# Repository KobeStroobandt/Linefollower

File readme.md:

# LineFollower

lege repository die je als template kan gebruiken om een eigen repository te starten voor uw linefollower project

## specifications

microcontroller: ESP32 S3

motors: Aslong JGA12-N20-30

h-bridge: TB6612FNG

sensors: Polulu QTR 8

batteries: 1800 Top Fuel

wireless communication: Wifi

distance sensor - motors: 7cm

weight: 0.5 kg

speed: 0.56 m/s

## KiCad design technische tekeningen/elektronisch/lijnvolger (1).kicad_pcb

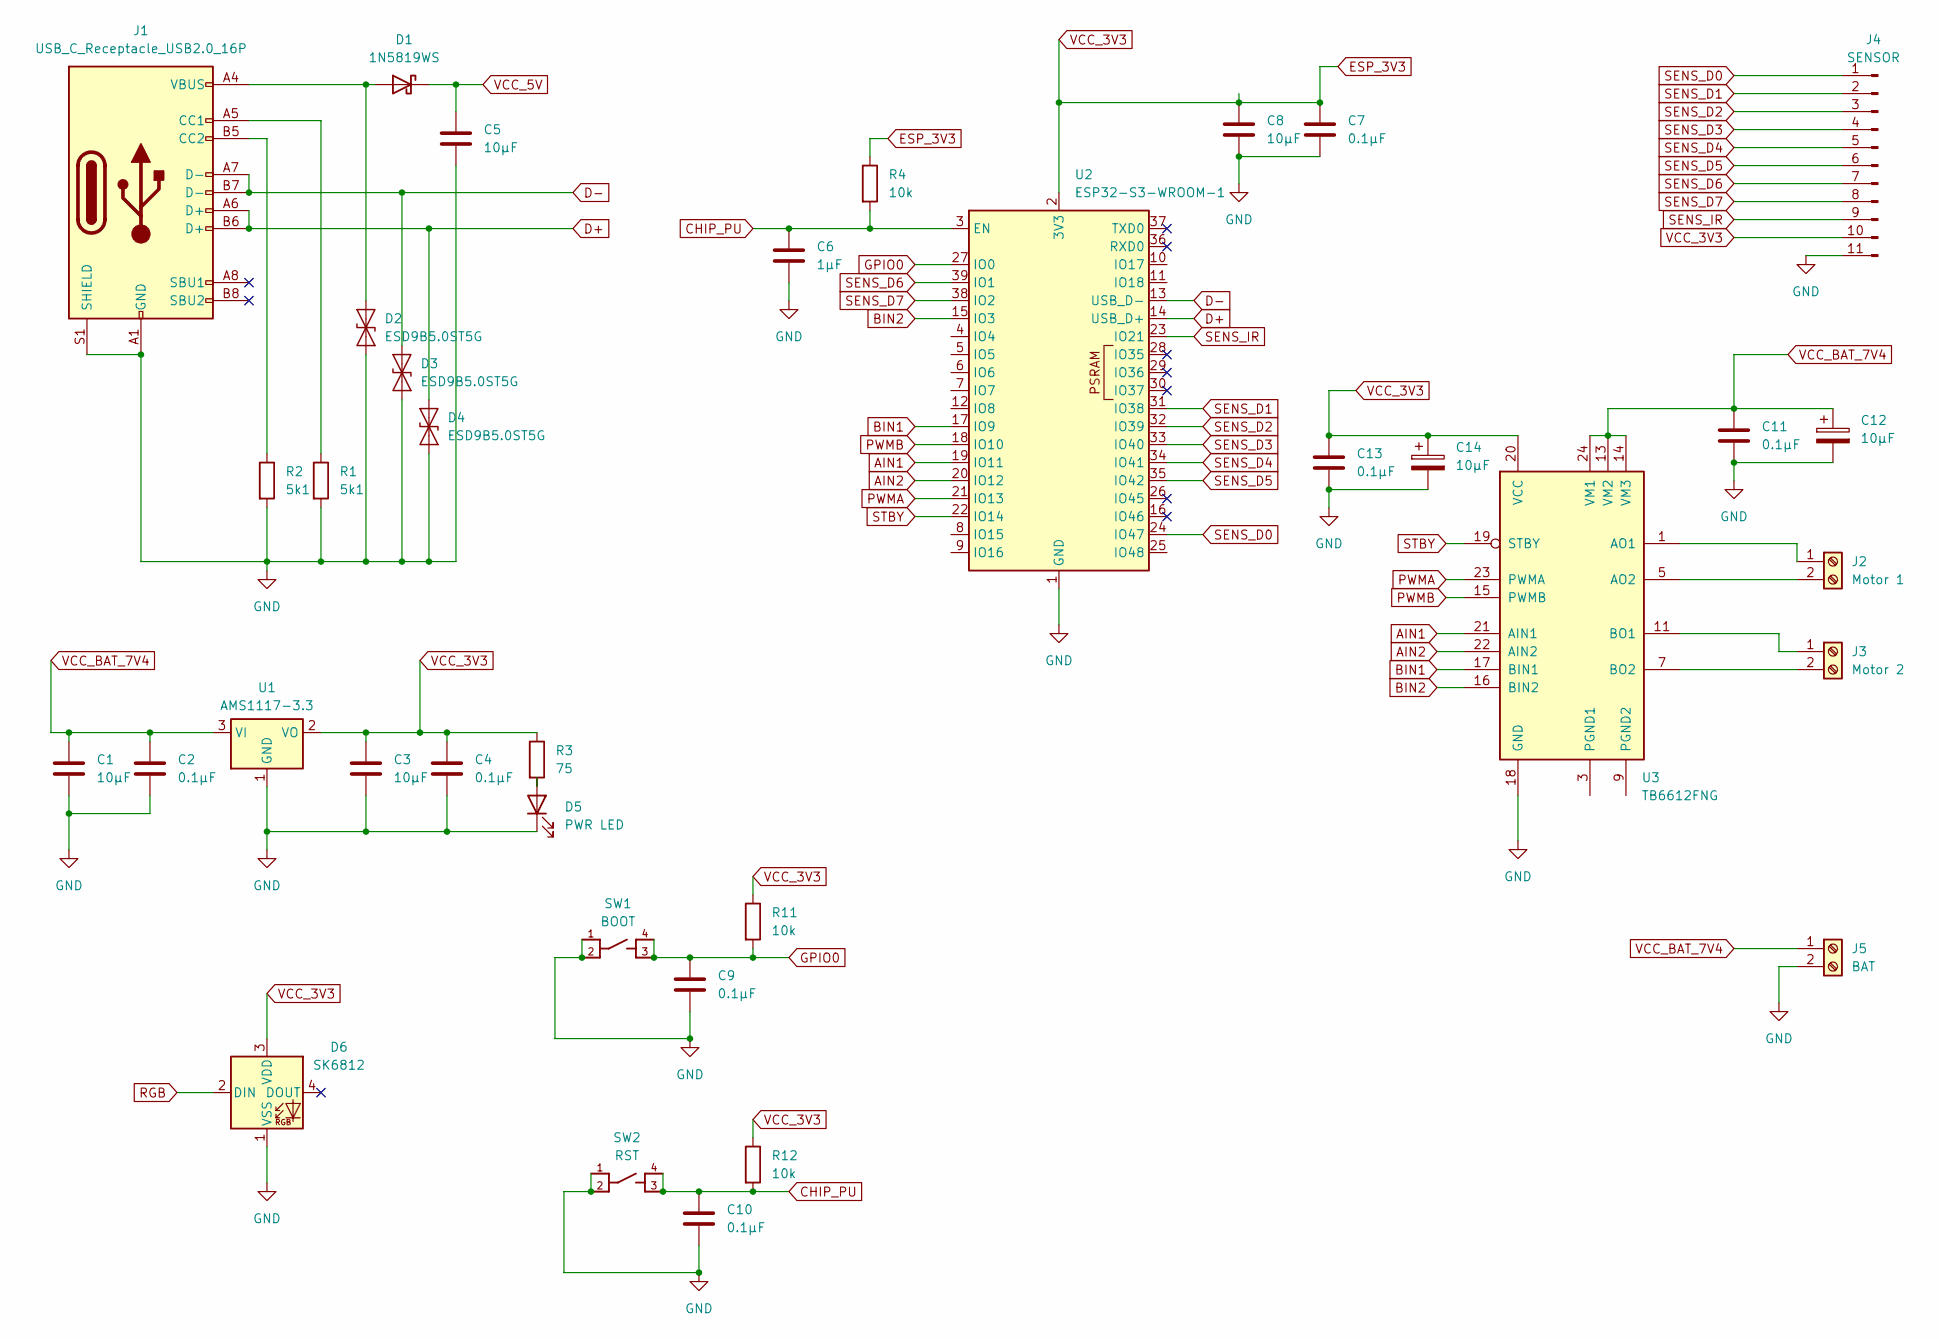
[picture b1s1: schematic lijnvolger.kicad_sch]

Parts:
C1, C3, C5, C8, C12, C14: 10µF; C_0805_2012Metric
C2, C4, C7, C9, C10: 0.1µF; C_0603_1608Metric
C6: 1µF; C_0603_1608Metric
C11, C13: 0.1µF; C_0805_2012Metric
D1: 1N5819WS; D_SOD-323
D2, D3, D4: ESD9B5.0ST5G; D_SOD-923
D5: PWR LED; LED_0201_0603Metric
D6: SK6812; LED_SK6812_PLCC4_5.0x5.0mm_P3.2mm
J1: USB_C_Receptacle_USB2.0_16P; USB_C_Receptacle_HRO_TYPE-C-31-M-12
J2: Motor 1; TerminalBlock_Phoenix_MKDS-1,5-2-5.08_1x02_P5.08mm_Horizont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
J3: Motor 2; TerminalBlock_Phoenix_MKDS-1,5-2-5.08_1x02_P5.08mm_Horizont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
J4: SENSOR; PinHeader_1x11_P1.00mm_Vertical
J5: BAT; TerminalBlock_Phoenix_MKDS-1,5-2-5.08_1x02_P5.08mm_Horizont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
R1, R2: 5k1; R_0805_2012Metric
R3: 75; R_0805_2012Metric
R4, R11, R12: 10k; R_0603_1608Metric
SW1: BOOT; SW_PTS810_SJM_250_SMTR_LFS
SW2: RST; SW_PTS810_SJM_250_SMTR_LFS
U1: AMS1117-3.3; SOT-223-3_TabPin2
U2: ESP32-S3-WROOM-1
U3: TB6612FNG; SSOP-24_5.3x8.2mm_P0.65mm

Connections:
AIN1: U2.19 (IO11), U3.21 (AIN1)
AIN2: U2.20 (IO12), U3.22 (AIN2)
BIN1: U2.17 (IO9), U3.17 (BIN1)
BIN2: U2.15 (IO3), U3.16 (BIN2)
CHIP_PU: C6.1, C10.1, R4.2, R12.2, SW2.3, SW2.4, U2.3 (EN)
D+: D4.1 (A1), J1.A6 (D+), J1.B6 (D+), U2.14 (USB_D+)
D-: D3.1 (A1), J1.A7 (D-), J1.B7 (D-), U2.13 (USB_D-)
ESP_3V3: C3.1, C4.1, C7.1, C8.1, C13.1, C14.1, D6.3 (VDD), J4.10, R3.1, R4.1, R11.1, R12.1, U1.2 (VO), U2.2 (3V3), U3.20 (VCC)
GND: C1.2, C2.2, C3.2, C4.2, C5.2, C6.2, C7.2, C8.2, C9.2, C10.2, C11.2, C12.2, C13.2, C14.2, D2.2 (A2), D3.2 (A2), D4.2 (A2), D5.1 (K), D6.1 (VSS), J1.A1 (GND), J1.A12 (GND), J1.B1 (GND), J1.B12 (GND), J1.S1 (SHIELD), J4.11, J5.2, R1.2, R2.2, SW1.1, SW1.2, SW2.1, SW2.2, U1.1 (GND), U2.1 (GND), U2.40 (GND), U2.41 (GND), U3.18 (GND)
GPIO0: C9.1, R11.2, SW1.3, SW1.4, U2.27 (IO0)
unnamed: D1.2 (A), D2.1 (A1), J1.A4 (VBUS), J1.A9 (VBUS), J1.B4 (VBUS), J1.B9 (VBUS)
unnamed: D5.2 (A), R3.2
unnamed: J1.A5 (CC1), R1.1
unnamed: J1.B5 (CC2), R2.1
unnamed: J2.1, U3.1 (AO1), U3.2 (AO1)
unnamed: J2.2, U3.5 (AO2), U3.6 (AO2)
unnamed: J3.1, U3.11 (BO1), U3.12 (BO1)
unnamed: J3.2, U3.7 (BO2), U3.8 (BO2)
unnamed: U3.3 (PGND1), U3.4 (PGND1)
unnamed: U3.9 (PGND2), U3.10 (PGND2)
PWMA: U2.21 (IO13), U3.23 (PWMA)
PWMB: U2.18 (IO10), U3.15 (PWMB)
RGB: D6.2 (DIN)
SENS_D0: J4.1, U2.24 (IO47)
SENS_D1: J4.2, U2.31 (IO38)
SENS_D2: J4.3, U2.32 (IO39)
SENS_D3: J4.4, U2.33 (IO40)
SENS_D4: J4.5, U2.34 (IO41)
SENS_D5: J4.6, U2.35 (IO42)
SENS_D6: J4.7, U2.39 (IO1)
SENS_D7: J4.8, U2.38 (IO2)
SENS_IR: J4.9, U2.23 (IO21)
STBY: U2.22 (IO14), U3.19 (STBY)
VCC_5V: C5.1, D1.1 (K)
VCC_BAT_7V4: C1.1, C2.1, C11.1, C12.1, J5.1, U1.3 (VI), U3.13 (VM2), U3.14 (VM3), U3.24 (VM1)

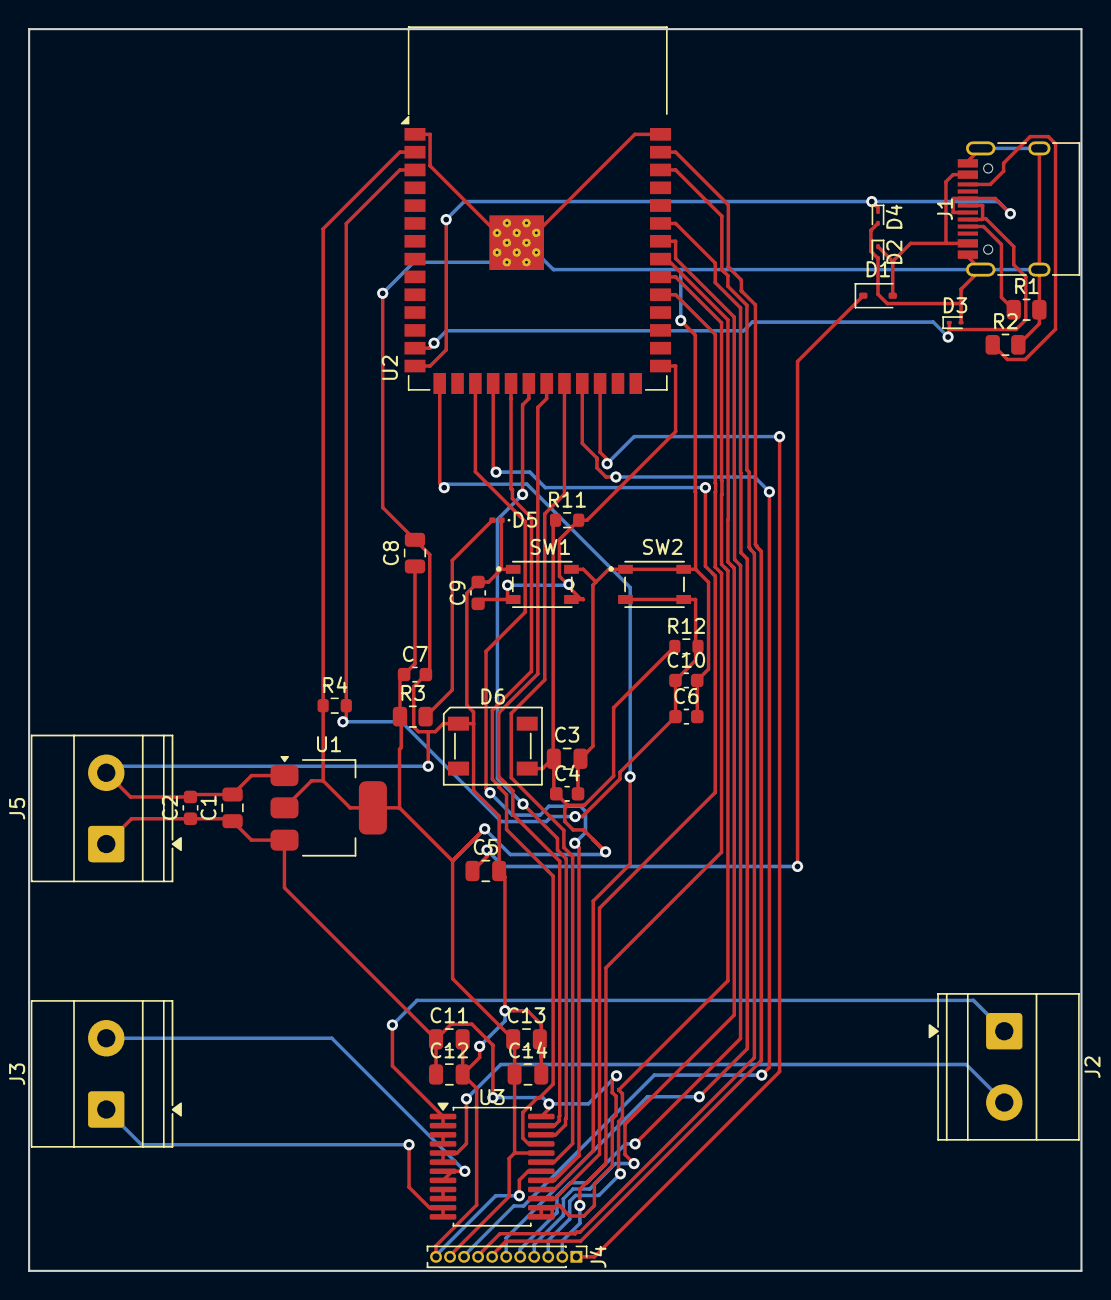
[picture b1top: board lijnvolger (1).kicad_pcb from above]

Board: 2 copper layers, 75.0 x 88.5 mm, 36 parts (0 on the bottom side), 34 nets.

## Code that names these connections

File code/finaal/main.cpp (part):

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const int offsetA = -1;
const int offsetB = 1;

#define AIN1 11
#define BIN1 9
#define AIN2 12
#define BIN2 3
#define PWMA 13
#define PWMB 10
#define STBY 14

Motor motor1 = Motor(AIN1, AIN2, PWMA, offsetA, STBY);
Motor motor2 = Motor(BIN1, BIN2, PWMB, offsetB, STBY);
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
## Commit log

2025-11-03 Create BOM
2025-11-03 Update BOM
2025-11-03 Rename BOM to BOM.md
2025-11-03 Create Specifications
2025-11-22 Create TB6612FNG
2025-11-22 Update TB6612FNG
2025-11-22 Create Software
2025-11-22 Update Software
2025-11-22 Rename Software to software.md
2025-11-22 Rename software.md to TB6612FNG Motorcontroller.md
2025-11-22 Rename TB6612FNG Motorcontroller.md to TB6612FNG.md
2025-11-22 Rename POC to POC.md
2025-12-14 Rename lijnvolger (3).kicad_sch to lijnvolger.kicad_sch
2025-12-14 Rename lijnvolger (1).kicad_pcb to lijnvolger.kicad_pcb
2025-12-14 Rename KicadScreenshot.png to KicadScreenshotSch.png
2025-12-14 Rename Schermafbeelding 2025-12-14 203741.png to KicadScreenshotPcb.png
2025-12-14 Rename Grand Kieran-Curcan(2).stl to Lijnvolger.stl
